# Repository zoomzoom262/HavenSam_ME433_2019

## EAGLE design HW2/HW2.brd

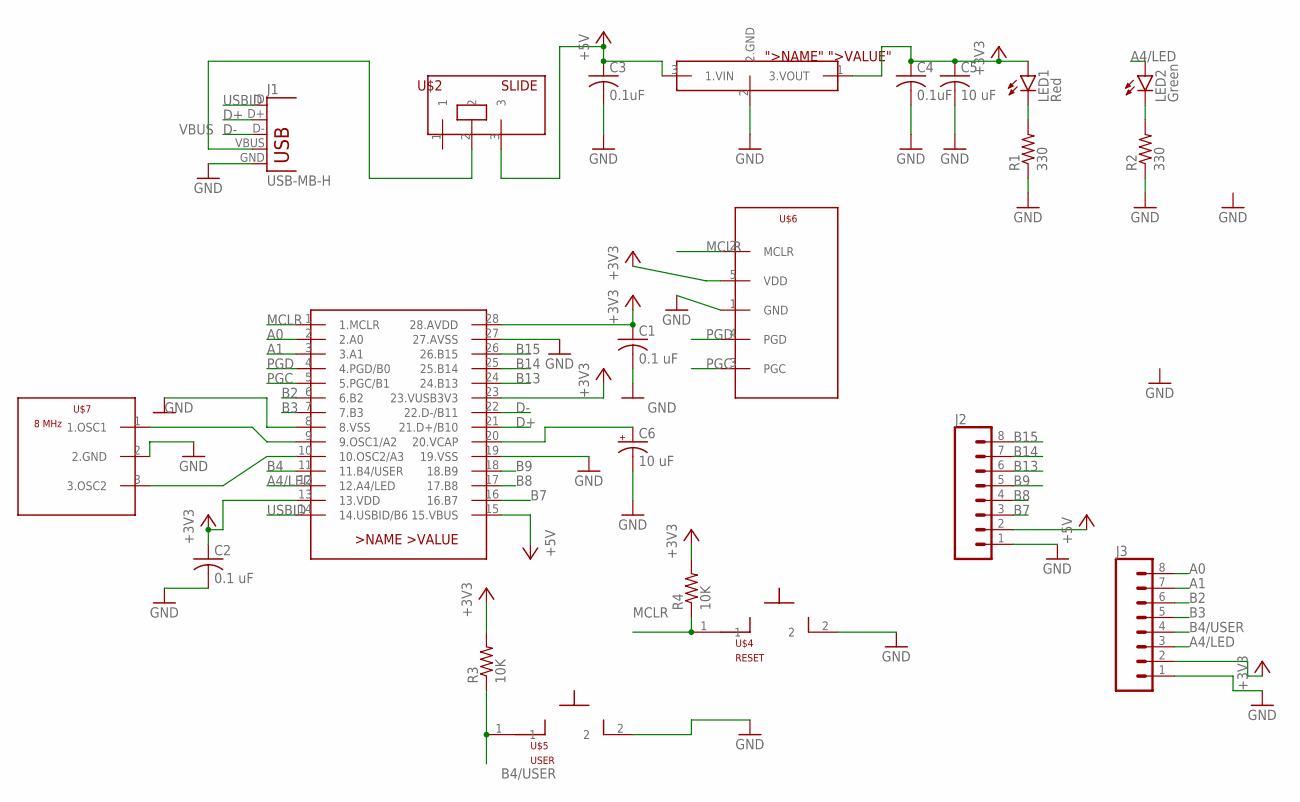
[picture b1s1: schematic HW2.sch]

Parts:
C1, C2: 0.1 uF; C025-025X050
C3, C4: 0.1uF; C025-025X050
C5: 10 uF; C025-025X050
C6: 10 uF; B45181B
J1: USB-MB-H
J2, J3: CONN_08"; 1X08
LED1: Red; LED3MM
LED2: Green; LED3MM
R1, R2: 330; 0207/10
R3, R4: 10K; 0207/10
U$1: PIC32MX270F256D; DIL28-3
U$2: SLIDE
U$3: L4931; TO92
U$4: RESET; PB
U$5: USER; PB
U$6: PICKIT3; 1X05
U$7: 8 MHz; OSC

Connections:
+3V3: C1.1, C2.1, C4.1, C5.1, J3.2, LED1.A, R3.2, R4.2, U$1.13 (13.VDD), U$1.23 (23.VUSB3V3), U$1.28 (28.AVDD), U$3.1 (3.VOUT), U$6.5 (VDD)
+5V: C3.1, J2.2, U$1.15 (15.VBUS), U$2.3, U$3.3 (1.VIN)
A0: J3.8, U$1.2 (2.A0)
A1: J3.7, U$1.3 (3.A1)
A4/LED: J3.3, LED2.A, U$1.12 (12.A4/LED)
B2: J3.6, U$1.6 (6.B2)
B3: J3.5, U$1.7 (7.B3)
B4: U$1.11 (11.B4/USER)
B4/USER: J3.4, R3.1, U$5.1
B7: J2.3, U$1.16 (16.B7)
B8: J2.4, U$1.17 (17.B8)
B9: J2.5, U$1.18 (18.B9)
B13: J2.6, U$1.24 (24.B13)
B14: J2.7, U$1.25 (25.B14)
B15: J2.8, U$1.26 (26.B15)
D+: J1.D+, U$1.21 (21.D+/B10)
D-: J1.D-, U$1.22 (22.D-/B11)
GND: C1.2, C2.2, C3.2, C4.2, C5.2, C6.-, J1.GND, J2.1, J3.1, R1.1, R2.1, U$1.8 (8.VSS), U$1.19 (19.VSS), U$1.27 (27.AVSS), U$3.2 (2.GND), U$4.2, U$5.2, U$6.1 (GND), U$7.2 (2.GND)
MCLR: R4.1, U$1.1 (1.MCLR), U$4.1, U$6.2 (MCLR)
unnamed: LED2.K (C), R2.2
unnamed: LED1.K (C), R1.2
unnamed: U$1.9 (9.OSC1/A2), U$7.1 (1.OSC1)
unnamed: U$1.10 (10.OSC2/A3), U$7.3 (3.OSC2)
unnamed: C6.+, U$1.20 (20.VCAP)
PGC: U$1.5 (5.PGC/B1), U$6.3 (PGC)
PGD: U$1.4 (4.PGD/B0), U$6.4 (PGD)
USBID: J1.ID, U$1.14 (14.USBID/B6)
VBUS: J1.VBUS, U$2.2

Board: 2 copper layers, 22 parts (0 on the bottom side), 27 nets, no tracks yet.

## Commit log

2019-04-09 Create HW1
    make HW1
2019-04-09 Create main.c
    create main.c
2019-04-09 Clear auto created code
    clear auto created code
2019-04-09 Insert template code into main.c
    insert template
2019-04-09 update #pragmas
    update #pragmas
2019-04-09 Update main.c
    update
2019-04-10 Create HW2
    create file
2019-04-10 idk
    idk
2019-04-11 Test with Josh PCB
    switch pin numbers back (B4 and A4)
2019-04-11 Add circuit diagram
2019-04-11 HW2 Big Dump
    Completed library and schematic
2019-04-11 work on board
    still looks like shit
